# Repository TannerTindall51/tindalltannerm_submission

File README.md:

# tindalltannerm_submission

Name: Tanner Tindall
Email: tindat1@unlv.nevada.edu
Student ID: 8000733733

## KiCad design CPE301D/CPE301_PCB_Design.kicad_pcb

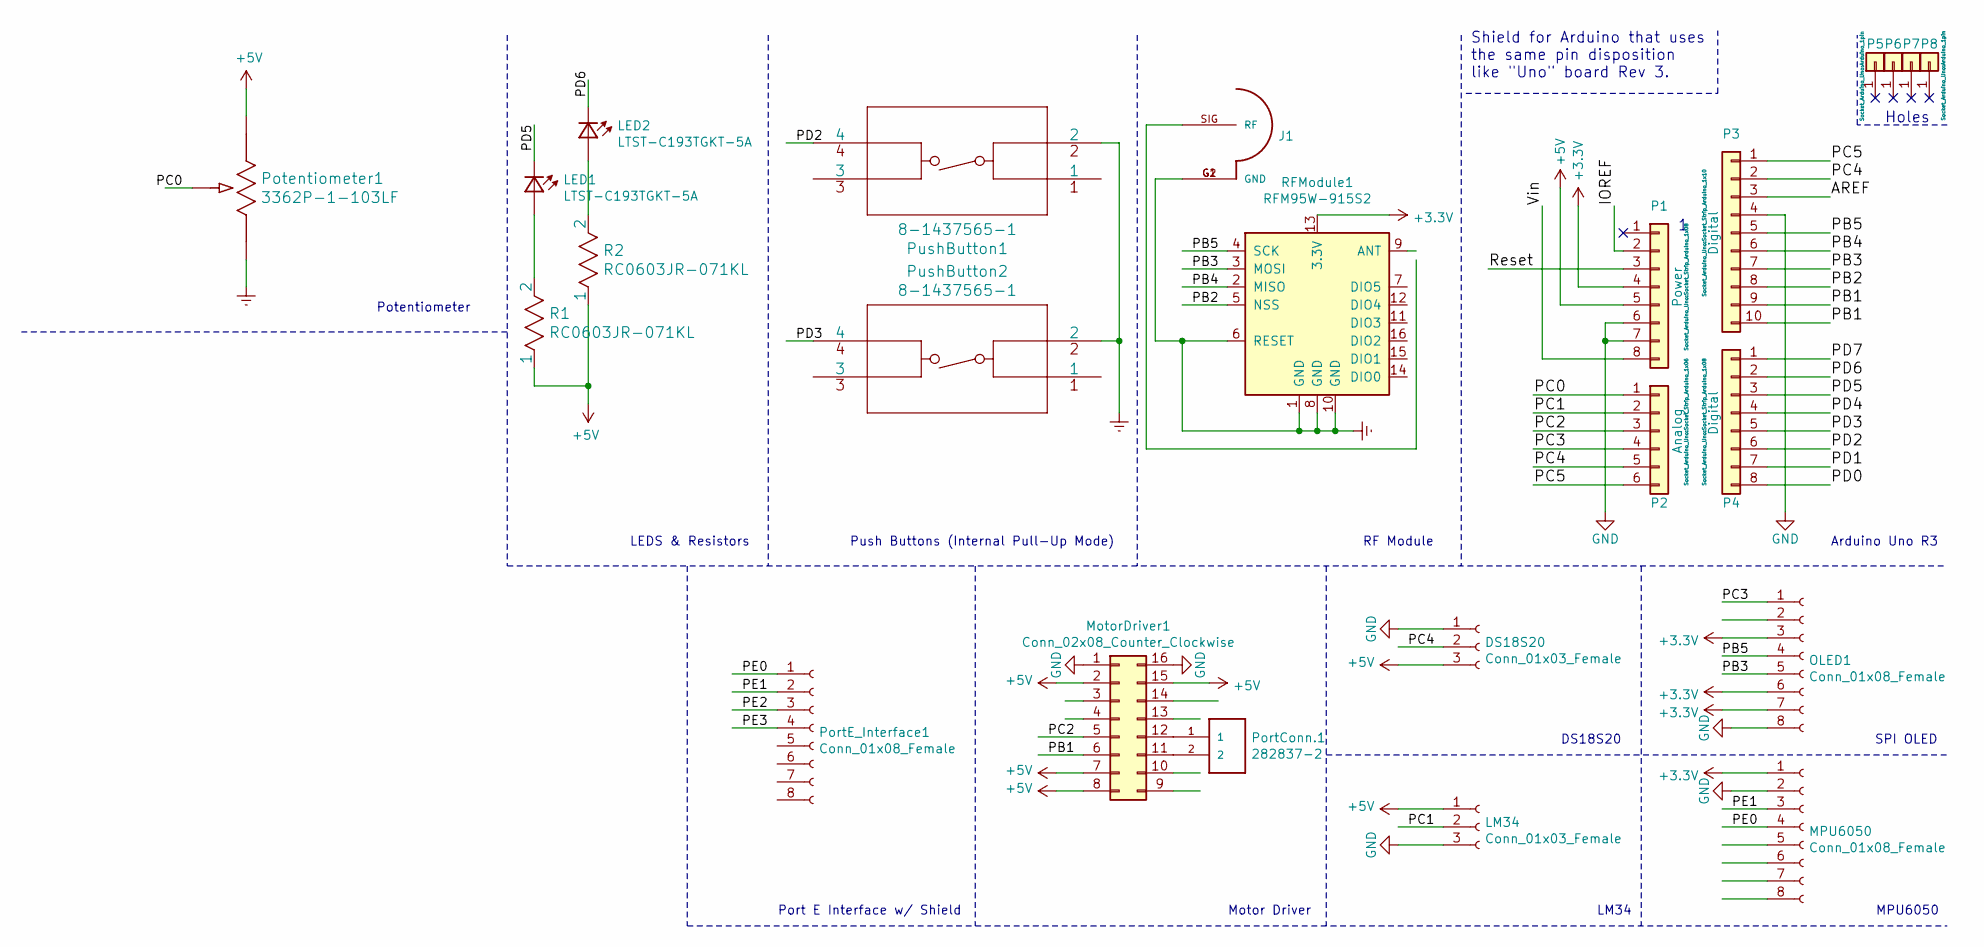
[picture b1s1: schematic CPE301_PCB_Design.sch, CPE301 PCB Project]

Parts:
DS18S20: Conn_01x03_Female; PinSocket_1x03_P1.27mm_Vertical
J1: CONUFL001-SMD; U.FL
LED1, LED2: LTST-C193TGKT-5A; 0603
LM34: Conn_01x03_Female; PinSocket_1x03_P1.27mm_Vertical
MPU6050: Conn_01x08_Female; PinSocket_1x08_P1.27mm_Vertical
MotorDriver1: Conn_02x08_Counter_Clockwise; motDrive2
OLED1: Conn_01x08_Female; Socket_Strip_Arduino_1x08
P1: Power; Socket_Strip_Arduino_1x08
P2: Analog; Socket_Strip_Arduino_1x06
P3: Digital; Socket_Strip_Arduino_1x10
P4: Digital; Socket_Strip_Arduino_1x08
P5, P6, P7, P8: CONN_01X01; Arduino_1pin
PortConn.1: 282837-2; TE_282837-2
PortE_Interface1: Conn_01x08_Female; Socket_Strip_Arduino_1x08
Potentiometer1: 3362P-1-103LF
PushButton1, PushButton2: 8-1437565-1
R1, R2: RC0603JR-071KL
RFModule1: RFM95W-915S2; XCVR_RFM95W-915S2

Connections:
+3V3: MPU6050.1, OLED1.3, OLED1.6, OLED1.7, P1.4, RFModule1.13 (3.3V)
+5V: DS18S20.3, LM34.1, MotorDriver1.2, MotorDriver1.7, MotorDriver1.8, MotorDriver1.15, P1.5, Potentiometer1.3, R1.1, R2.1
/AREF: P3.3
/IOREF: P1.2
/PB1: MotorDriver1.6, P3.9, P3.10
/PB2: P3.8, RFModule1.5 (NSS)
/PB3: OLED1.5, P3.7, RFModule1.3 (MOSI)
/PB4: P3.6, RFModule1.2 (MISO)
/PB5: OLED1.4, P3.5, RFModule1.4 (SCK)
/PC0: P2.1, Potentiometer1.2
/PC1: LM34.2, P2.2
/PC2: MotorDriver1.5, P2.3
/PC3: OLED1.1, P2.4
/PC4: DS18S20.2, P2.5, P3.2
/PC5: P2.6, P3.1
/PD0: P4.8
/PD1: P4.7
/PD2: P4.6, PushButton1.4
/PD3: P4.5, PushButton2.4
/PD4: P4.4
/PD5: LED1.1 (K2), P4.3
/PD6: LED2.1 (K2), P4.2
/PD7: P4.1
/PE0: MPU6050.4, PortE_Interface1.1
/PE1: MPU6050.3, PortE_Interface1.2
/PE2: PortE_Interface1.3
/PE3: PortE_Interface1.4
/Reset: P1.3
/Vin: P1.8
Earth: J1.G1 (GND), J1.G2 (GND), Potentiometer1.1, PushButton1.2, PushButton2.2, RFModule1.1 (GND), RFModule1.6 (RESET), RFModule1.8 (GND), RFModule1.10 (GND)
GND: DS18S20.1, LM34.3, MPU6050.2, MotorDriver1.1, MotorDriver1.16, OLED1.8, P1.6, P1.7, P3.4
unnamed: LED1.2 (A2), R1.2
unnamed: LED2.2 (A2), R2.2
unnamed: MotorDriver1.11, PortConn.1.2
unnamed: MotorDriver1.12, PortConn.1.1

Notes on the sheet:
Holes
Shield for Arduino that uses the same pin disposition like "Uno" board Rev 3.
RF Module
Arduino Uno R3
Push Buttons (Internal Pull-Up Mode)
LEDS & Resistors
Potentiometer
SPI OLED
MPU6050
DS18S20
LM34
Port E Interface w/ Shield
Motor Driver

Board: 2 copper layers, 24 parts (0 on the bottom side), 25 nets, no tracks yet.

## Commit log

2020-02-15 Create Design_Assignments
2020-02-15 Add files via upload
    Primary Code for Design Assignment 1
2020-02-22 Create DA1B

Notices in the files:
parts and their libraries:
Copyright 2016 Accelerated Designs. All rights reserved.
